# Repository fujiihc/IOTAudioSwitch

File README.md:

# IOTAudioSwitch
Google Home Compatible Audio Input Selector

## Overview
I created this switcher because I have too many audio inputs (CD Player, Turntable, Google Chromecast Audio), and only one set of speakers.

I also had recently acquired a Google Home Nest and wanted to experiment with ESP32 Dev Boards.

I found that using Google Home to control input switching was way more convenient than having to get up and manually plug things into my speakers.

The switching is done with a [CD4052B Multiplexor](https://www.ti.com/lit/ds/symlink/cd4052b.pdf?ts=1735797913372&ref_url=https%253A%252F%252Fwww.ti.com.cn%252Fproduct%252Fcn%252FCD4052B0).
## Future Plans
Create a version WITHOUT Arduino Cloud using different [ESP32 Microcontroller](https://www.amazon.com/DORHEA-Development-Microcontroller-NodeMCU-32S-ESP-WROOM-32/dp/B086MJGFVV/ref=pd_ci_mcx_mh_mcx_views_0_title?pd_rd_w=nsGng&content-id=amzn1.sym.bb21fc54-1dd8-448e-92bb-2ddce187f4ac%3Aamzn1.symc.40e6a10e-cbc4-4fa5-81e3-4435ff64d03b&pf_rd_p=bb21fc54-1dd8-448e-92bb-2ddce187f4ac&pf_rd_r=E53KTVRRZ11WJPA49XZE&pd_rd_wg=QMCDy&pd_rd_r=7f830703-b24a-47aa-b2a2-523e741be20f&pd_rd_i=B086MJGFVV&th=1)

Look into Independent Power Supplies/Power Filtering

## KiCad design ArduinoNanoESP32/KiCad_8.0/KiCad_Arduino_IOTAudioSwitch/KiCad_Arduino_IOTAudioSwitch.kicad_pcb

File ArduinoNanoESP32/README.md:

# IOTAudioSwitch using Arduino Nano ESP32

## Overview
This version of the IOTAudioSwitch uses an Arduino Nano ESP32 as the microcontroller.

It is compatible with Google Home through [Arduino Cloud](https://cloud.arduino.cc/).
## Set Up

## Notes
The Schematic and PCB include traces connecting Pin 3 to INH.
This is never actually used for "Mute" functionality.
This can be removed and ignored due to Arduino Cloud "Cloud Variable" limitations.

## To-Do/Future Plans
Finish Custom PCB

Finish "Set Up" in README

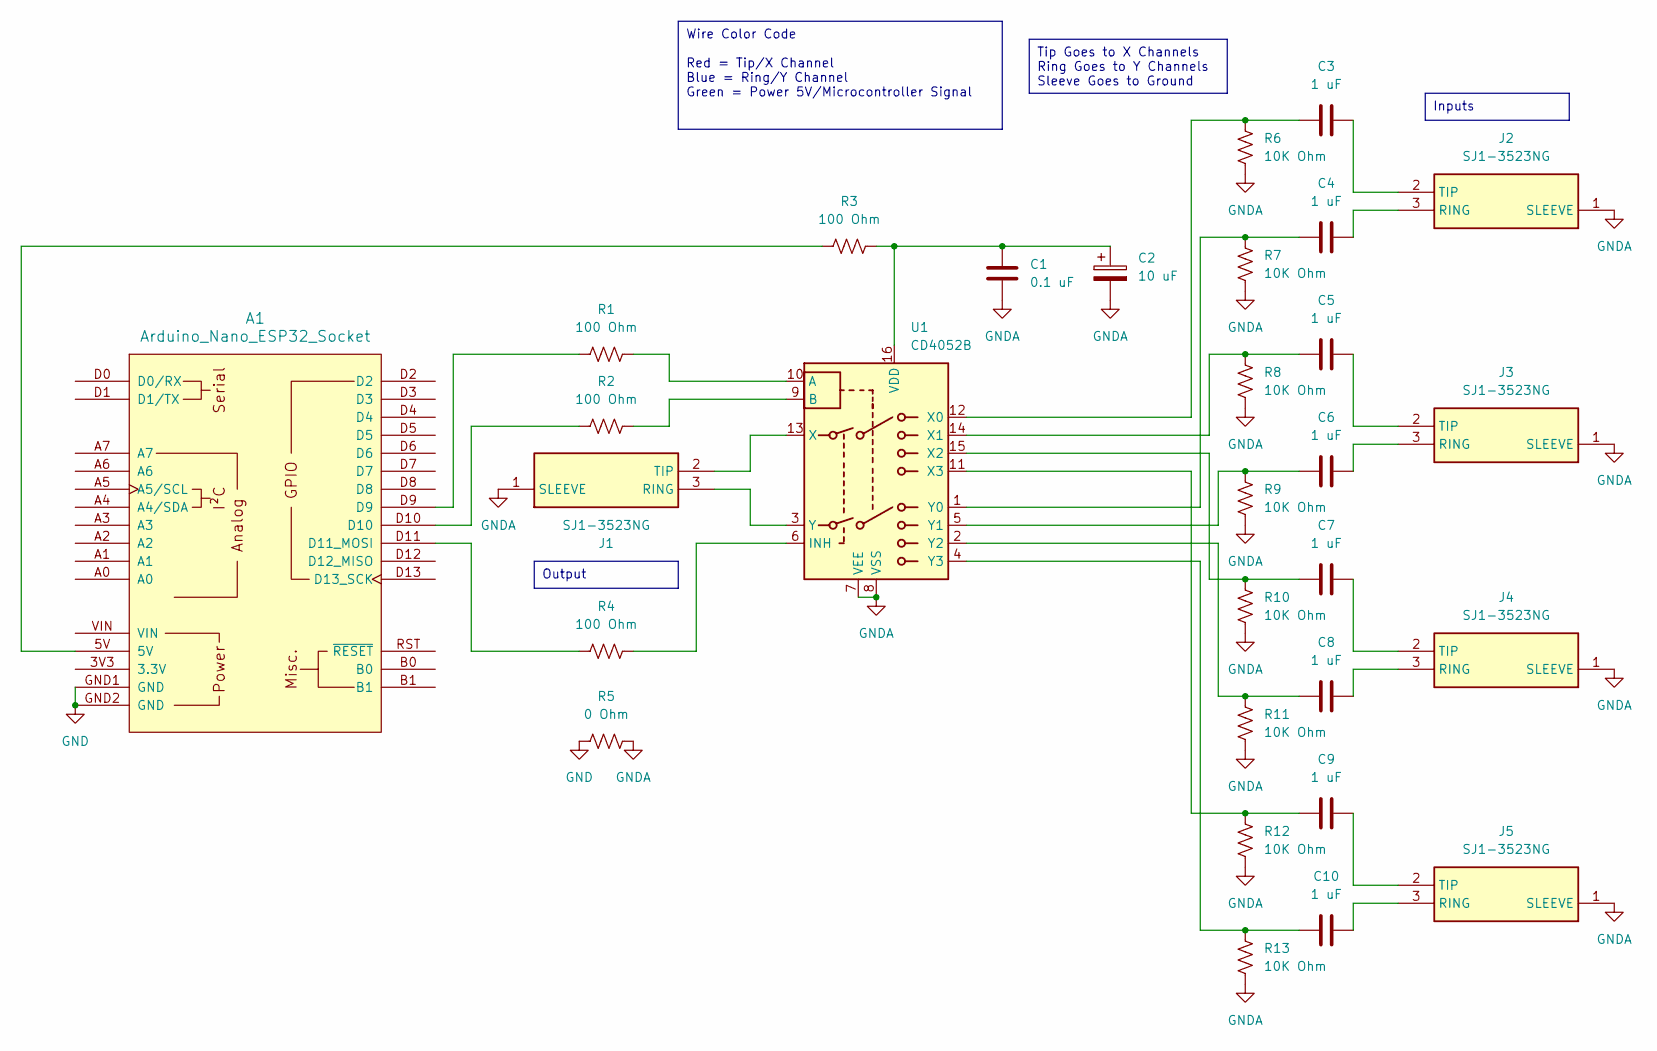
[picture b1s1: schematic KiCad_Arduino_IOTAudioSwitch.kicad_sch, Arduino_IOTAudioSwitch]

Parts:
A1: Arduino_Nano_ESP32_Socket
C1: 0.1 uF; C_Disc_D8.0mm_W2.5mm_P5.00mm
C2: 10 uF; CP_Radial_D5.0mm_P2.00mm
C3, C4, C5, C6, C7, C8, C9, C10: 1 uF; C_Disc_D8.0mm_W2.5mm_P5.00mm
J1, J2, J3, J4, J5: SJ1-3523NG; SJ13523NG; Mouser Part Number 490-SJ1-3523NG
R1, R2, R3, R4: 100 Ohm; R_Axial_DIN0207_L6.3mm_D2.5mm_P7.62mm_Horizontal
R5: 0 Ohm; R_Axial_DIN0207_L6.3mm_D2.5mm_P7.62mm_Horizontal
R6, R7, R8, R9, R10, R11, R12, R13: 10K Ohm; R_Axial_DIN0207_L6.3mm_D2.5mm_P7.62mm_Horizontal
U1: CD4052B; DIPS762W70P254L2032H510Q16N

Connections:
GND: A1.GND1 (GND), A1.GND2 (GND), R5.1
GNDA: C1.2, C2.2, J1.1 (SLEEVE), J2.1 (SLEEVE), J3.1 (SLEEVE), J4.1 (SLEEVE), J5.1 (SLEEVE), R5.2, R6.2, R7.2, R8.2, R9.2, R10.2, R11.2, R12.2, R13.2, U1.7 (VEE), U1.8 (VSS)
unnamed: A1.D11 (D11_MOSI), R4.1
unnamed: A1.5V, R3.1
unnamed: A1.D9, R1.1
unnamed: A1.D10, R2.1
unnamed: J1.3 (RING), U1.3 (Y)
unnamed: J1.2 (TIP), U1.13 (X)
unnamed: C4.2, J2.3 (RING)
unnamed: C3.2, J2.2 (TIP)
unnamed: C6.2, J3.3 (RING)
unnamed: C5.2, J3.2 (TIP)
unnamed: C8.2, J4.3 (RING)
unnamed: C7.2, J4.2 (TIP)
unnamed: C10.2, J5.3 (RING)
unnamed: C9.2, J5.2 (TIP)
unnamed: R1.2, U1.10 (A)
unnamed: R2.2, U1.9 (B)
unnamed: R4.2, U1.6 (INH)
unnamed: C1.1, C2.1, R3.2, U1.16 (VDD)
unnamed: C3.1, R6.1, U1.12 (X0)
unnamed: C5.1, R8.1, U1.14 (X1)
unnamed: C7.1, R10.1, U1.15 (X2)
unnamed: C9.1, R12.1, U1.11 (X3)
unnamed: C4.1, R7.1, U1.1 (Y0)
unnamed: C6.1, R9.1, U1.5 (Y1)
unnamed: C8.1, R11.1, U1.2 (Y2)
unnamed: C10.1, R13.1, U1.4 (Y3)

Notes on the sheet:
Wire Color Code Red = Tip/X Channel Blue = Ring/Y Channel Green = Power 5V/Microcontroller Signal
Output
Tip Goes to X Channels Ring Goes to Y Channels Sleeve Goes to Ground
Inputs

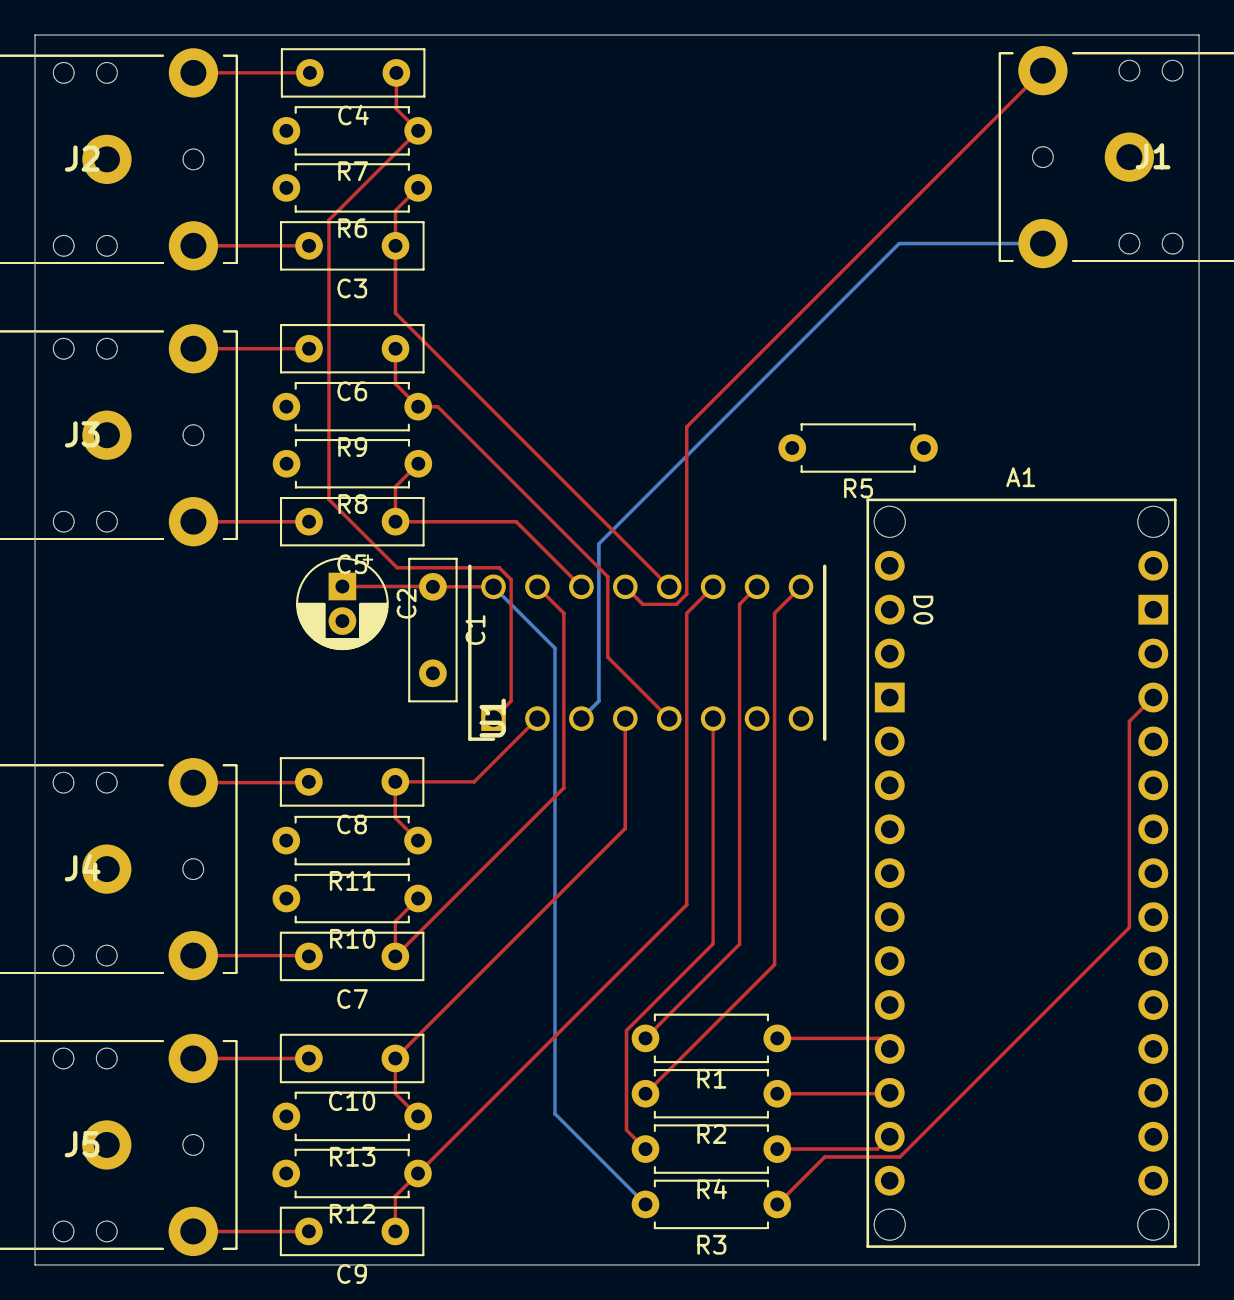
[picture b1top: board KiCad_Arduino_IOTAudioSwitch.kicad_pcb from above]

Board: 2 copper layers, 67.3 x 71.1 mm, 30 parts (0 on the bottom side), 28 nets.

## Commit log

2025-01-03 Added Arduino Code
2025-01-03 Added KiCad and Arduino Files
2025-01-16 Created PCB
